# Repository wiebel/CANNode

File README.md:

Homegrown CAN/OW based home automation.

https://wiebel.org/CANNode/

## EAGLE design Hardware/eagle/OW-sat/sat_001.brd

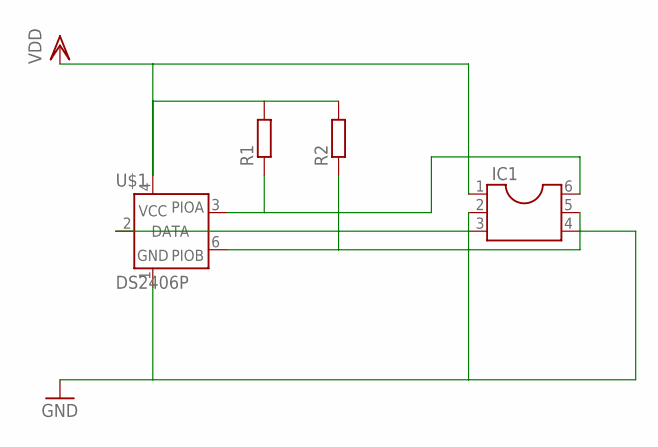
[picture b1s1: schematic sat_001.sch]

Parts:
IC1: DIL6; DIL06
R1, R2: R-EU_R0805; R0805
U$1: DS2406P; TSOC6

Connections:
GND: IC1.3, IC1.4, U$1.1 (GND)
unnamed: IC1.6, R1.1, U$1.3 (PIOA)
unnamed: IC1.5, R2.1, U$1.6 (PIOB)
unnamed: IC1.2, U$1.2 (DATA)
VDD: IC1.1, R1.2, R2.2, U$1.4 (VCC)

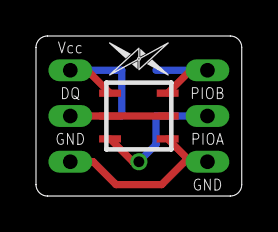
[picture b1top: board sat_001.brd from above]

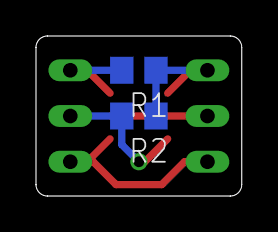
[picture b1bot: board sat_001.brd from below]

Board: 2 copper layers, 11.4 x 8.9 mm, 5 parts (2 on the bottom side), 5 nets.

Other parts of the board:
U$2: LOGO_SMAL

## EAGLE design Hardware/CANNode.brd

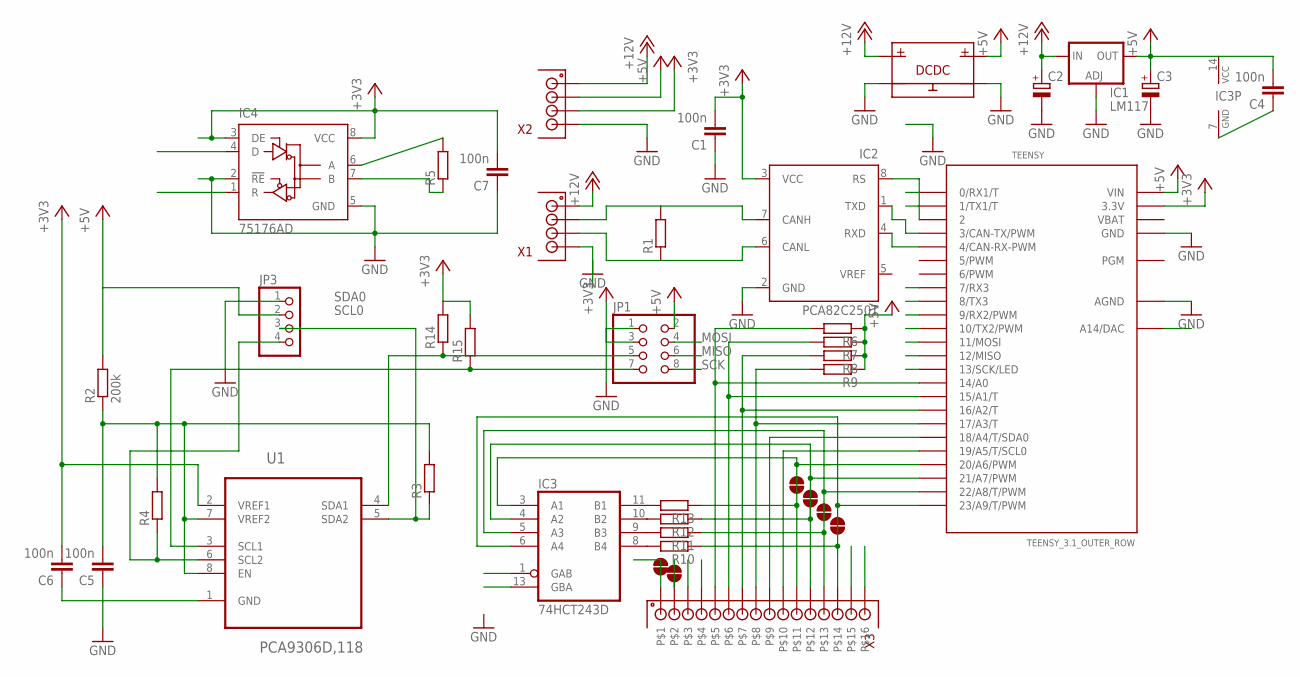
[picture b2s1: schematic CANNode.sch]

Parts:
C1, C4, C5, C6, C7: 100n; C0805
C2, C3: CPOL-EUA/3216-18W; A/3216-18W
IC1: LM117; SOT223
IC2: PCA82C250T; SO8
IC3: 74HCT243D; SO14
IC4: 75176AD; D_R-PDSO-G8
JP1: PINHD-2X4; 2X04
JP3: PINHD-1X4; 1X04
MOD1: DCDC; DC-DC
R1, R3, R4, R5, R6, R7, R8, R9, R10, R11, R12, R13, R14, R15: R-EU_R0805W; R0805W
R2: 200k; R0805W
TEENSY: TEENSY_3.1_OUTER_ROW; TEENSY3-OUTER_ROW
U1: PCA9306D,118; SOIC127P600X175-8N
U$2, U$3, U$4, U$5, U$14, U$15: 2-WAY_BRIDGE
X1, X2: KF141-P4; KF141V-P4
X3: KF141-P16; KF141V-P16

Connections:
+3V3: C1.2, C6.2, C7.2, IC2.3 (VCC), IC4.3 (DE), IC4.8 (VCC), JP1.3, R14.2, R15.2, TEENSY.3.3V, TEENSY.3.3V1 (3.3V), U1.2 (VREF1), X2.P$103, X2.P$203
+5V: C3.+, C4.2, IC1.4 (OUT), IC3.14 (VCC), JP1.2, JP3.2, MOD1.OUT+, R2.2, R6.1, R7.1, R8.1, R9.1, TEENSY.VIN, X2.P$102, X2.P$202
+12V: C2.+, IC1.3 (IN), MOD1.IN+, X1.P$101, X1.P$201, X2.P$101, X2.P$201
A14: TEENSY.RESET/DAC (A14/DAC), X3.P$103, X3.P$203
GND: C1.1, C2.-, C3.-, C4.1, C5.1, C6.1, C7.1, IC1.1 (ADJ), IC2.2 (GND), IC3.7 (GND), IC4.2 (!RE), IC4.5 (GND), JP1.1, JP3.1, MOD1.IN-, MOD1.OUT-, TEENSY.AGND, TEENSY.GND, TEENSY.GND1 (GND), U1.1 (GND), X1.P$104, X1.P$204, X2.P$104, X2.P$204
MISO: JP1.6, TEENSY.12 (12/MISO)
MOSI: JP1.4, TEENSY.11 (11/MOSI)
unnamed: IC2.1 (TXD), TEENSY.3 (3/CAN-TX/PWM)
unnamed: IC2.4 (RXD), TEENSY.4 (4/CAN-RX-PWM)
unnamed: IC2.7 (CANH), R1.2, X1.P$102, X1.P$202
unnamed: IC3.8 (B4), R10.2
unnamed: IC3.9 (B3), R11.2
unnamed: R12.1, U$3.B, X3.P$112, X3.P$212
unnamed: IC3.3 (A1), R13.1, TEENSY.20/A6 (20/A6/PWM), U$2.A, U$2.B, X3.P$111, X3.P$211
unnamed: IC3.10 (B2), R12.2
unnamed: IC2.8 (RS), TEENSY.2
unnamed: C5.2, R2.1, R3.2, R4.2, U1.7 (VREF2), U1.8 (EN)
unnamed: R9.2, TEENSY.17/A3 (17/A3/T), X3.P$108, X3.P$208
unnamed: R8.2, TEENSY.16/A2 (16/A2/T), X3.P$107, X3.P$207
unnamed: R7.2, TEENSY.15/A1 (15/A1/T), X3.P$106, X3.P$206
unnamed: R6.2, TEENSY.14/A0, X3.P$105, X3.P$205
unnamed: R10.1, U$5.B, X3.P$114, X3.P$214
unnamed: IC3.5 (A3), R11.1, TEENSY.22/A8 (22/A8/T/PWM), U$4.A, U$4.B, X3.P$113, X3.P$213
unnamed: IC3.4 (A2), TEENSY.21/A7 (21/A7/PWM), U$3.A
unnamed: IC2.6 (CANL), R1.1, X1.P$103, X1.P$203
unnamed: IC3.11 (B1), R13.2
unnamed: IC3.6 (A4), TEENSY.23/A9 (23/A9/T/PWM), U$5.A
RX1: TEENSY.0 (0/RX1/T), X3.P$116, X3.P$216
RX2: IC4.1 (R), IC4.6 (A), R5.2, TEENSY.9 (9/RX2/PWM), U$15.A, U$15.B, X3.P$102, X3.P$202
RX3: IC3.13 (GBA), TEENSY.7 (7/RX3)
SCK: JP1.8, TEENSY.13 (13/SCK/LED), X3.P$104, X3.P$204
SCL0: JP1.7, R15.1, TEENSY.19/A5 (19/A5/T/SCL0), U1.3 (SCL1), X3.P$110, X3.P$210
SCL_5V: JP3.4, R4.1, U1.6 (SCL2)
SDA0: JP1.5, R14.1, TEENSY.18/A4 (18/A4/T/SDA0), U1.4 (SDA1), X3.P$109, X3.P$209
SDA_5V: JP3.3, R3.1, U1.5 (SDA2)
TX1: TEENSY.1 (1/TX1/T), X3.P$115, X3.P$215
TX2: IC4.4 (D), IC4.7 (B), R5.1, TEENSY.10 (10/TX2/PWM), U$14.A, U$14.B, X3.P$101, X3.P$201
TX3: IC3.1 (GAB), TEENSY.8 (8/TX3)
VBAT: TEENSY.VBAT

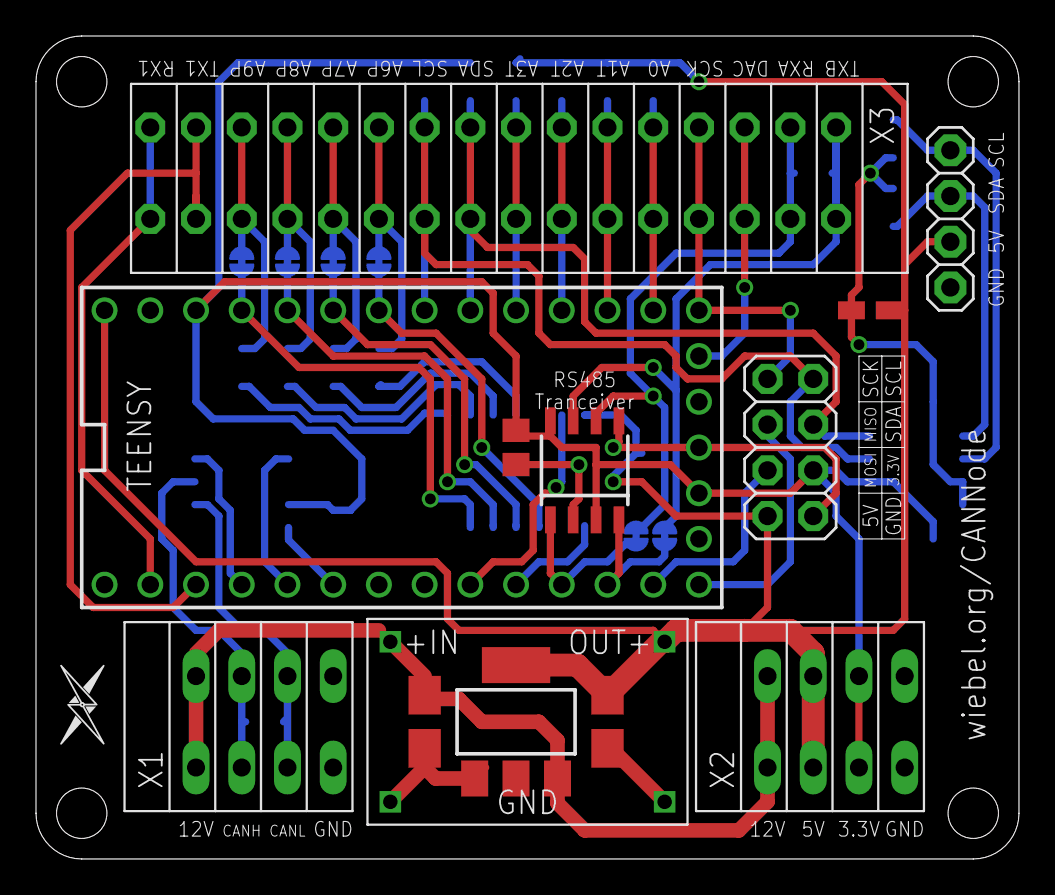
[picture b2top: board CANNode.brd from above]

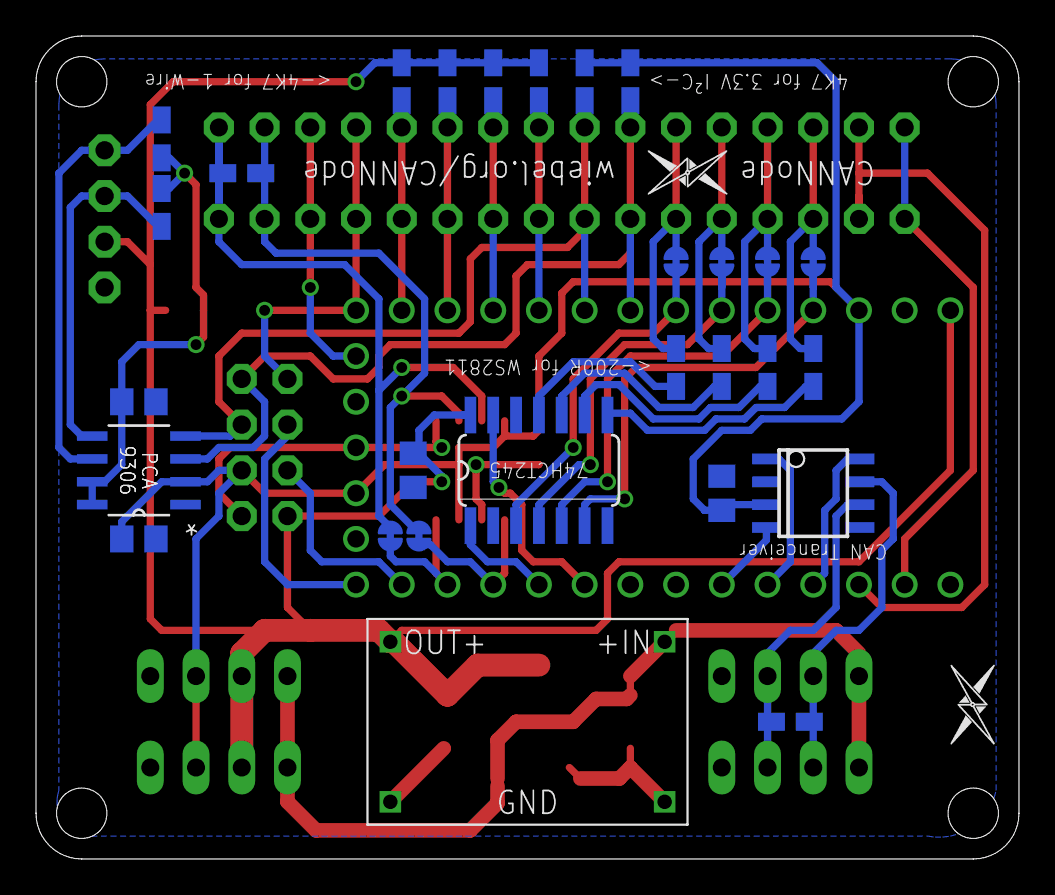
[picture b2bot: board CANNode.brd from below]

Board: 2 copper layers, 54.6 x 45.7 mm, 43 parts (29 on the bottom side), 38 nets.

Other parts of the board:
U$1, U$6, U$7: LOGO_MID

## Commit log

2016-05-30 initial
2016-05-30 Latest
2016-06-01 getting structurerered
2016-06-01 state change implemented
2016-06-02 first CAN light ;)
2016-06-03 renamed (see PCB)
2016-06-03 cleanup
2016-06-03 added Hardware sources
2016-06-03 Added Schematic as png
2016-06-11 now with response and remote switching
2016-07-24 starting with output
2016-09-09 in progress
2016-09-09 Compiling again
2016-09-14 It Works !!
2016-09-18 Before can send rewrite
2016-09-18 kinda working, still queing problems
2016-09-18 Great success, read and write buffering CAN wise
2016-09-18 first Switches
2016-09-19 tuning starts
2016-09-24 Productive
2016-09-25 iworking 2
2016-09-27 better initialization, consistant switches
2017-01-15 Before ModularizatioBefore Modularizationn
2017-01-15 new external node definition
2017-02-15 node 3 went life
2017-02-15 improved error handling of OW devices
2017-03-22 Configurrations
2017-03-22 mirror test
2017-03-22 mirror test 02
2017-03-22 Revert "mirror test"
    This reverts commit f052826ef3645006a35cdb1b423a686126aebfa9.
2017-07-25 latest addition (rolladen, Terasse)
2017-09-21 new node and FastLED
2017-10-02 git test
2017-10-02 Revert "new node and FastLED"
    This reverts commit 4730087f9e0407dac3795dfea3b10a3f22bc8b54.
2017-10-05 Revert "latest addition (rolladen, Terasse)"
    This reverts commit 26ac6558e48cb40bebec67ddc240ef2eee2f421f.
2017-10-05 Revert "git test"
    This reverts commit f4ac188a96c213f6665db2e03689f4f45f09be38.
2018-01-19 Latest addition WZ switch
2018-03-01 Refinements
2018-03-01 push test
2018-03-07 Add 'README.md'
    Started a README
2018-03-07 More to READ
2018-08-20 new images
2018-09-14 Create LICENSE
2018-10-30 More talking to CAN (state change, new TWids)
2018-11-12 rev2 started on kicad
2018-11-13 kicad 101
2018-11-15 Rearranging
2018-11-16 almost routed
2018-11-17 looks good
2018-11-17 images
2018-11-17 late changes
2018-11-17 images from oshpark
2018-11-22 Licenced by CC
2018-11-22 more clearance in Layer 2
2018-11-22 cleanup after order
2018-11-22 images moved to webroot
2018-11-22 corrected output port labels
2018-12-03 ena I²C text
2019-03-17 new switch in WZ
2019-03-20 more feedback in and out
2019-03-24 added some tools
2019-03-28 more tools
2019-04-01 added affinity groups
2019-04-02 much better can bus writing
2019-09-02 last before adding current sensors
2019-10-22 First current messurement attempts
2019-10-22 new images (pdf)
2019-11-16 double RS485
2019-11-16 second RS485 swapped with OW
2019-12-15 latest changes in tools
2019-12-16 fixed loop for shutter2can
2019-12-16 updated coilmap
2019-12-29 some toole refinery
2019-12-29 new alli in one, 001
2020-01-15 try for command to fix failure in unknowtry for command to fix failure in unknownn
2020-02-25 latest additions
2020-07-01 pproaching v2.5
2021-02-18 PCB fixed silkscreen
